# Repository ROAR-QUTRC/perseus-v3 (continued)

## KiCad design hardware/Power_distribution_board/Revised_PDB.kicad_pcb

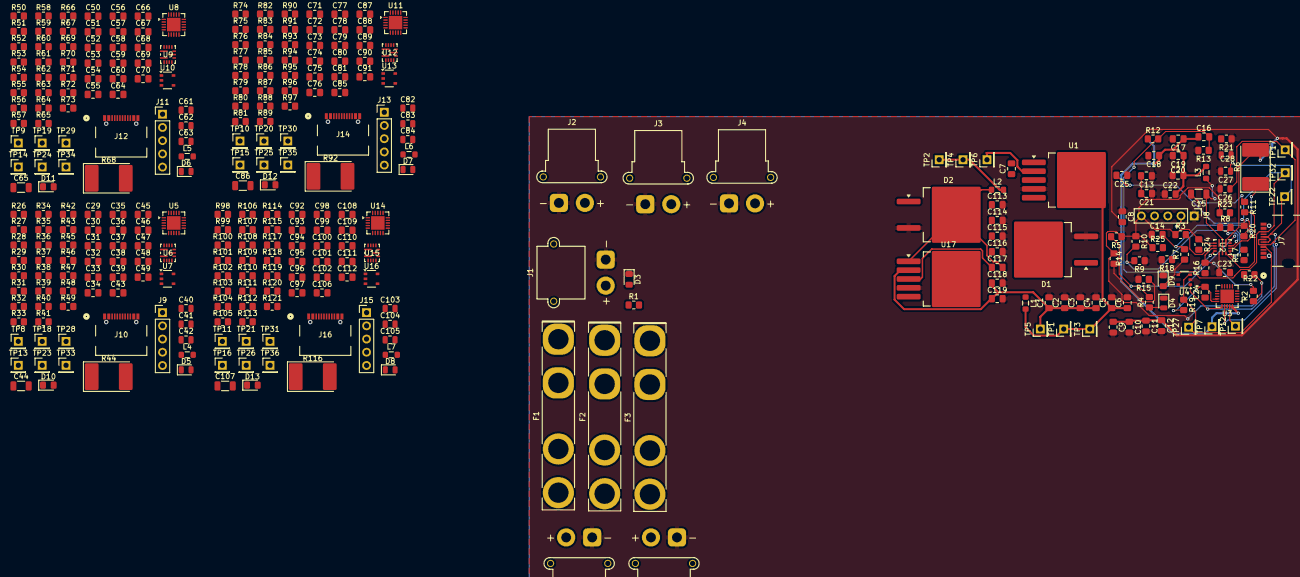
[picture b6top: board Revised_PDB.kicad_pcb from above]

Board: 4 copper layers, 332 parts (0 on the bottom side), 174 nets.

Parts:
C1, C2, C3, C115, C116, C118: 15u; C_0805_2012Metric_Pad1.18x1.45mm_HandSolder
C4, C119: 0.47u; C_0805_2012Metric_Pad1.18x1.45mm_HandSolder
C5, C6, C113, C114: 180u; C_0805_2012Metric_Pad1.18x1.45mm_HandSolder
C7, C117: 0.01u; C_0805_2012Metric_Pad1.18x1.45mm_HandSolder
C8, C31, C52, C73, C94: 100u; C_0805_2012Metric_Pad1.18x1.45mm_HandSolder
C9, C10, C11, C17, C18, C19, C32, C33, C35, C46, C47, C48, C53, C54, C56, C67, C68, C69, C74, C75, C77, C88, C89, C90, C95, C96, C98, C109, C110, C111: 10u; C_0805_2012Metric_Pad1.18x1.45mm_HandSolder
C12, C39, C60, C81, C102: 100n; C_0805_2012Metric_Pad1.18x1.45mm_HandSolder
C13, C21, C22, C29, C30, C38, C50, C51, C59, C71, C72, C80, C92, C93, C101: 2.2u; C_0805_2012Metric_Pad1.18x1.45mm_HandSolder
C14, C45, C66, C87, C108: 1nF; C_0805_2012Metric_Pad1.18x1.45mm_HandSolder
C15, C44, C65, C86, C107: 1u; C_1206_3216Metric
C16, C43, C64, C85, C106: 22pF; C_0805_2012Metric_Pad1.18x1.45mm_HandSolder
C20, C49, C70, C91, C112: 47u; C_0805_2012Metric_Pad1.18x1.45mm_HandSolder
C23, C34, C55, C76, C97: 470n; C_0805_2012Metric_Pad1.18x1.45mm_HandSolder
C24, C25, C36, C37, C57, C58, C78, C79, C99, C100: 390p; C_0805_2012Metric_Pad1.18x1.45mm_HandSolder
C26, C27, C40, C41, C61, C62, C82, C83, C103, C104: 1n; C_0805_2012Metric
C28, C42, C63, C84, C105: 10n; C_0805_2012Metric
D1, D2: 6TQ035S; TO-263-2
D3, D9, D10, D11, D12, D13: LED; LED_0805_2012Metric_Pad1.15x1.40mm_HandSolder
D4, D5, D6, D7, D8: LED; LED_0805_2012Metric
F1, F2: 5A; Fuseholder_Keystone_3555-2
F3: 20A; Fuseholder_Keystone_3555-2
J1: xt30_PWR_IN; AMASS_XT30PW-M_1x02_P2.50mm_Horizontal
J2, J3, J4, J5, J6: XT30_VOUT1; AMASS_XT30PW-F_1x02_P2.50mm_Horizontal
J7, J10, J12, J14, J16: USB_C_Receptacle_USB2.0_16P; USB4105_GCT
J8, J9, J11, J13, J15: Conn_01x05; PinHeader_1x05_P2.54mm_Vertical
L1, L2: L; L_0805_2012Metric_Pad1.05x1.20mm_HandSolder
L3, L4, L5, L6, L7: 4.7u; L_0805_2012Metric_Pad1.05x1.20mm_HandSolder
R1, R18, R30, R54, R78, R102: R; R_0805_2012Metric_Pad1.20x1.40mm_HandSolder
R2, R3, R31, R36, R55, R60, R79, R84, R103, R108: 10k; R_0805_2012Metric_Pad1.20x1.40mm_HandSolder
R4, R5, R39, R40, R63, R64, R87, R88, R111, R112: 2.2k; R_0805_2012Metric_Pad1.20x1.40mm_HandSolder
R6, R44, R68, R92, R116: 300k; D_3220_8050Metric_Pad2.65x5.15mm_HandSolder
R7, R47, R71, R95, R119: 6.8k; R_0805_2012Metric_Pad1.20x1.40mm_HandSolder
R8, R43, R67, R91, R115: 51k; R_0805_2012Metric_Pad1.20x1.40mm_HandSolder
R9, R11, R16, R17, R28, R29, R42, R49, R52, R53, R66, R73, R76, R77, R90, R97, R100, R101, R114, R121: 0; R_0805_2012Metric_Pad1.20x1.40mm_HandSolder
R10, R14, R15, R22, R23, R24, R25, R26, R27, R32, R33, R34, R35, R48, R50, R51, R56, R57, R58, R59, R72, R74, R75, R80, R81, R82, R83, R96, R98, R99, R104, R105, R106, R107, R120: DNF; R_0805_2012Metric_Pad1.20x1.40mm_HandSolder
R12, R45, R69, R93, R117: 100k; R_0805_2012Metric_Pad1.20x1.40mm_HandSolder
R13, R46, R70, R94, R118: 11k; R_0805_2012Metric_Pad1.20x1.40mm_HandSolder
R19, R20, R37, R38, R61, R62, R85, R86, R109, R110: 2.2; R_0805_2012Metric_Pad1.20x1.40mm_HandSolder
R21, R41, R65, R89, R113: 1M; R_0805_2012Metric_Pad1.20x1.40mm_HandSolder
TP1, TP2: Feeback; PinHeader_1x01_P2.54mm_Vertical
TP3, TP4: VOUT; PinHeader_1x01_P2.54mm_Vertical
TP5, TP6: VIN; PinHeader_1x01_P2.54mm_Vertical
TP7, TP8, TP9, TP10, TP11: VBUS; PinHeader_1x01_P2.54mm_Vertical
TP12, TP13, TP14, TP15, TP16: VDRV; PinHeader_1x01_P2.54mm_Vertical
TP17, TP18, TP19, TP20, TP21: DM; PinHeader_1x01_P2.54mm_Vertical
TP22, TP23, TP24, TP25, TP26: DP; PinHeader_1x01_P2.54mm_Vertical
TP27, TP28, TP29, TP30, TP31: CC1; PinHeader_1x01_P2.54mm_Vertical
TP32, TP33, TP34, TP35, TP36: CC2; PinHeader_1x01_P2.54mm_Vertical
U1, U17: LM2678SX-12_NOPB; TO-263-5_TabPin6
U2, U6, U9, U12, U15: MP2491CGQB-Z; QFN-13_2p5MMx3MM_MNP
U3, U5, U8, U11, U14: MP5031GRE-00A3-P; QFN-20-1EP_4x4mm_P0.5mm_EP2.6x2.6mm
U4, U7, U10, U13, U16: TPD4E1U06DBVR; TSOP-5_1.65x3.05mm_P0.95mm

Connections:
+5V: C13.2, C21.2, C29.2, C38.2, C50.2, C59.2, C71.2, C80.2, C92.2, C101.2, J8.5, J9.5, J11.5, J13.5, J15.5, R2.1, R3.1, R5.1, R10.1, R14.1, R22.1, R23.1, R24.1, R25.1, R26.1, R31.1, R32.1, R33.1, R34.1, R35.1, R36.1, R40.1, R48.1, R50.1, R55.1, R56.1, R57.1, R58.1, R59.1, R60.1, R64.1, R72.1, R74.1, R79.1, R80.1, R81.1, R82.1, R83.1, R84.1, R88.1, R96.1, R98.1, R103.1, R104.1, R105.1, R106.1, R107.1, R108.1, R112.1, R120.1, U2.3 (VCC), U3.7 (VCC), U5.7 (VCC), U6.3 (VCC), U8.7 (VCC), U9.3 (VCC), U11.7 (VCC), U12.3 (VCC), U14.7 (VCC), U15.3 (VCC)
/12 Volt Reg1/VOUT: C113.1, C114.1, F2.1, L2.2, TP2.1 (1_1), TP4.1 (1_1), U17.6 (FB)
/12 Volt Reg/VIN: C1.1, C2.1, C3.1, C4.1, C115.1, C116.1, C118.1, C119.1, F3.2, J2.2, J3.2, J4.2, R1.2, TP5.1 (1_1), TP6.1 (1_1), U1.2 (INPUT), U17.2 (INPUT)
/12 Volt Reg/VOUT: C5.1, C6.1, F1.1, L1.2, TP1.1 (1_1), TP3.1 (1_1), U1.6 (FB)
/USB_pd1/GPIO2: R32.2, U5.11 (GPIO2)
/USB_pd1/GPIO3: R33.2, U5.9 (GPIO3)
/USB_pd1/GPIO4: R34.2, U5.10 (GPIO4)
/USB_pd1/GPIO5: R35.2, U5.4 (GPIO5)
/USB_pd1/PG: R39.2, R40.2, U6.13 (PG)
/USB_pd1/SCL: J9.2, U5.2 (SCL)
/USB_pd1/SDA: J9.3, U5.1 (SDA)
/USB_pd1/VIN: C31.2, C32.1, C33.1, C35.1, C39.1, R44.2, U6.1 (IN)
/USB_pd1/VSEL1: R29.2, R36.2, U6.4 (VSEL1)
/USB_pd1/VSEL2: R28.2, R31.2, U6.5 (VSEL2)
/USB_pd2/GPIO2: R56.2, U8.11 (GPIO2)
/USB_pd2/GPIO3: R57.2, U8.9 (GPIO3)
/USB_pd2/GPIO4: R58.2, U8.10 (GPIO4)
/USB_pd2/GPIO5: R59.2, U8.4 (GPIO5)
/USB_pd2/PG: R63.2, R64.2, U9.13 (PG)
/USB_pd2/SCL: J11.2, U8.2 (SCL)
/USB_pd2/SDA: J11.3, U8.1 (SDA)
/USB_pd2/VIN: C52.2, C53.1, C54.1, C56.1, C60.1, R68.2, U9.1 (IN)
/USB_pd2/VSEL1: R53.2, R60.2, U9.4 (VSEL1)
/USB_pd2/VSEL2: R52.2, R55.2, U9.5 (VSEL2)
/USB_pd3/GPIO2: R80.2, U11.11 (GPIO2)
/USB_pd3/GPIO3: R81.2, U11.9 (GPIO3)
/USB_pd3/GPIO4: R82.2, U11.10 (GPIO4)
/USB_pd3/GPIO5: R83.2, U11.4 (GPIO5)
/USB_pd3/PG: R87.2, R88.2, U12.13 (PG)
/USB_pd3/SCL: J13.2, U11.2 (SCL)
/USB_pd3/SDA: J13.3, U11.1 (SDA)
/USB_pd3/VIN: C73.2, C74.1, C75.1, C77.1, C81.1, R92.2, U12.1 (IN)
/USB_pd3/VSEL1: R77.2, R84.2, U12.4 (VSEL1)
/USB_pd3/VSEL2: R76.2, R79.2, U12.5 (VSEL2)
/USB_pd4/GPIO2: R104.2, U14.11 (GPIO2)
/USB_pd4/GPIO3: R105.2, U14.9 (GPIO3)
/USB_pd4/GPIO4: R106.2, U14.10 (GPIO4)
/USB_pd4/GPIO5: R107.2, U14.4 (GPIO5)
/USB_pd4/PG: R111.2, R112.2, U15.13 (PG)
/USB_pd4/SCL: J15.2, U14.2 (SCL)
/USB_pd4/SDA: J15.3, U14.1 (SDA)
/USB_pd4/VIN: C94.2, C95.1, C96.1, C98.1, C102.1, R116.2, U15.1 (IN)
/USB_pd4/VSEL1: R101.2, R108.2, U15.4 (VSEL1)
/USB_pd4/VSEL2: R100.2, R103.2, U15.5 (VSEL2)
/USB_pd/GPIO2: R22.2, U3.11 (GPIO2)
/USB_pd/GPIO3: R23.2, U3.9 (GPIO3)
/USB_pd/GPIO4: R24.2, U3.10 (GPIO4)
/USB_pd/GPIO5: R25.2, U3.4 (GPIO5)
/USB_pd/PG: R4.2, R5.2, U2.13 (PG)
/USB_pd/SCL: J8.2, U3.2 (SCL)
/USB_pd/SDA: J8.3, U3.1 (SDA)
/USB_pd/VIN: C8.2, C9.1, C10.1, C11.1, C12.1, R6.2, U2.1 (IN)
/USB_pd/VSEL1: R3.2, R17.2, U2.4 (VSEL1)
/USB_pd/VSEL2: R2.2, R16.2, U2.5 (VSEL2)
GND: C1.2, C2.2, C3.2, C4.2, C5.2, C6.2, C8.1, C9.2, C10.2, C11.2, C12.2, C13.1, C14.1, C17.2, C18.2, C19.2, C20.2, C21.1, C22.1, C23.1, C24.1, C25.1, C26.2, C27.2, C28.2, C29.1, C30.1, C31.1, C32.2, C33.2, C34.1, C35.2, C36.1, C37.1, C38.1, C39.2, C40.2, C41.2, C42.2, C45.1, C46.2, C47.2, C48.2, C49.2, C50.1, C51.1, C52.1, C53.2, C54.2, C55.1, C56.2, C57.1, C58.1, C59.1, C60.2, C61.2, C62.2, C63.2, C66.1, C67.2, C68.2, C69.2, C70.2, C71.1, C72.1, C73.1, C74.2, C75.2, C76.1, C77.2, C78.1, C79.1, C80.1, C81.2, C82.2, C83.2, C84.2, C87.1, C88.2, C89.2, C90.2, C91.2, C92.1, C93.1, C94.1, C95.2, C96.2, C97.1, C98.2, C99.1, C100.1, C101.1, C102.2, C103.2, C104.2, C105.2, C108.1, C109.2, C110.2, C111.2, C112.2, C113.2, C114.2, C115.2, C116.2, C118.2, C119.2, D1.3 (A), D2.3 (A), D3.1 (K), D4.1 (K), D5.1 (K), D6.1 (K), D7.1 (K), D8.1 (K), D9.1 (K), D10.1 (K), D11.1 (K), D12.1 (K), D13.1 (K), J1.1, J2.1, J3.1, J4.1, J5.1, J6.1, J8.1, J9.1, J11.1, J13.1, J15.1, R8.1, R9.1, R13.2, R15.2, R18.2, R21.1, R27.2, R30.2, R41.1, R43.1, R46.2, R49.1, R51.2, R54.2, R65.1, R67.1, R70.2, R73.1, R75.2, R78.2, R89.1, R91.1, R94.2, R97.1, R99.2, R102.2, R113.1, R115.1, R118.2, R121.1, U1.4 (GND), U2.2 (PGND), U2.7 (AGND), U4.2, U6.2 (PGND), U6.7 (AGND), U7.2, U9.2 (PGND), U9.7 (AGND), U10.2, U12.2 (PGND), U12.7 (AGND), U13.2, U15.2 (PGND), U15.7 (AGND), U16.2, U17.4 (GND)
unnamed: C15.2, R11.1
unnamed: C44.2, R42.1
unnamed: C65.2, R66.1
unnamed: C86.2, R90.1
unnamed: C107.2, R114.1
unnamed: C7.2, D1.2 (K), L1.1, U1.1 (SWITCH_OUTPUT)
unnamed: C117.2, D2.2 (K), L2.1, U17.1 (SWITCH_OUTPUT)
unnamed: D3.2 (A), R1.1
unnamed: D4.2 (A), R4.1
unnamed: D5.2 (A), R39.1
unnamed: D6.2 (A), R63.1
unnamed: D7.2 (A), R87.1
unnamed: D8.2 (A), R111.1
unnamed: D9.2 (A), R7.1
unnamed: D10.2 (A), R47.1
unnamed: D11.2 (A), R71.1
unnamed: D12.2 (A), R95.1
unnamed: D13.2 (A), R119.1
unnamed: F3.1, J1.2
unnamed: F1.2, J5.2
unnamed: F2.2, J6.2
unnamed: J7.A5 (CC1), R19.1, TP27.1 (1_1), U4.3
unnamed: J7.B5 (CC2), R20.1, TP32.1 (1_1), U4.4
unnamed: C28.1, R21.2
unnamed: J8.4, R18.1, U3.5 (I2C_MODE)
unnamed: J9.4, R30.1, U5.5 (I2C_MODE)
unnamed: J10.A5 (CC1), R37.1, TP28.1 (1_1), U7.3
unnamed: J10.B5 (CC2), R38.1, TP33.1 (1_1), U7.4
unnamed: C42.1, R41.2
unnamed: J11.4, R54.1, U8.5 (I2C_MODE)
unnamed: J12.A5 (CC1), R61.1, TP29.1 (1_1), U10.3
unnamed: J12.B5 (CC2), R62.1, TP34.1 (1_1), U10.4
unnamed: C63.1, R65.2
unnamed: J13.4, R78.1, U11.5 (I2C_MODE)
unnamed: J14.A5 (CC1), R85.1, TP30.1 (1_1), U13.3
unnamed: J14.B5 (CC2), R86.1, TP35.1 (1_1), U13.4
unnamed: C84.1, R89.2
unnamed: J15.4, R102.1, U14.5 (I2C_MODE)
unnamed: J16.A5 (CC1), R109.1, TP31.1 (1_1), U16.3
unnamed: J16.B5 (CC2), R110.1, TP36.1 (1_1), U16.4
unnamed: C105.1, R113.2
unnamed: C7.1, U1.3 (CB)
unnamed: R11.2, U2.9 (BST)
unnamed: C14.2, R6.1, R7.2, U2.11 (EN)
unnamed: C16.2, R12.2, R13.1, U2.6 (FB)
unnamed: R8.2, U2.12 (ILIM)
unnamed: R9.2, R10.2, U2.10 (MODE)
unnamed: C15.1, L3.1, U2.8 (SW)
unnamed: C24.2, R19.2, U3.15 (CC1)
unnamed: C25.2, R20.2, U3.14 (CC2)
unnamed: C26.1, J7.A7 (D-), J7.B7 (D-), TP17.1 (1_1), U3.17 (DM)
unnamed: C27.1, J7.A6 (D+), J7.B6 (D+), TP22.1 (1_1), U3.16 (DP), U4.1
unnamed: R17.1, U3.3 (GPIO1)
unnamed: R16.1, U3.12 (GPIO6)
unnamed: R14.2, R15.1, U3.13 (NTC)
unnamed: C23.2, U3.6 (VDD)
unnamed: TP12.1 (1_1), U3.19 (VDRV)
unnamed: C36.2, R37.2, U5.15 (CC1)
unnamed: C37.2, R38.2, U5.14 (CC2)
unnamed: C40.1, J10.A7 (D-), J10.B7 (D-), TP18.1 (1_1), U5.17 (DM)
unnamed: C41.1, J10.A6 (D+), J10.B6 (D+), TP23.1 (1_1), U5.16 (DP), U7.1
unnamed: R29.1, U5.3 (GPIO1)
unnamed: R28.1, U5.12 (GPIO6)
unnamed: R26.2, R27.1, U5.13 (NTC)
unnamed: C34.2, U5.6 (VDD)
unnamed: TP13.1 (1_1), U5.19 (VDRV)
unnamed: R42.2, U6.9 (BST)
unnamed: C45.2, R44.1, R47.2, U6.11 (EN)
unnamed: C43.2, R45.2, R46.1, U6.6 (FB)
unnamed: R43.2, U6.12 (ILIM)
unnamed: R48.2, R49.2, U6.10 (MODE)
unnamed: C44.1, L4.1, U6.8 (SW)
unnamed: C57.2, R61.2, U8.15 (CC1)
unnamed: C58.2, R62.2, U8.14 (CC2)
unnamed: C61.1, J12.A7 (D-), J12.B7 (D-), TP19.1 (1_1), U8.17 (DM)
unnamed: C62.1, J12.A6 (D+), J12.B6 (D+), TP24.1 (1_1), U8.16 (DP), U10.1
unnamed: R53.1, U8.3 (GPIO1)
unnamed: R52.1, U8.12 (GPIO6)
unnamed: R50.2, R51.1, U8.13 (NTC)
unnamed: C55.2, U8.6 (VDD)
unnamed: TP14.1 (1_1), U8.19 (VDRV)
unnamed: R66.2, U9.9 (BST)
unnamed: C66.2, R68.1, R71.2, U9.11 (EN)
unnamed: C64.2, R69.2, R70.1, U9.6 (FB)
unnamed: R67.2, U9.12 (ILIM)
unnamed: R72.2, R73.2, U9.10 (MODE)
unnamed: C65.1, L5.1, U9.8 (SW)
unnamed: C78.2, R85.2, U11.15 (CC1)
unnamed: C79.2, R86.2, U11.14 (CC2)
unnamed: C82.1, J14.A7 (D-), J14.B7 (D-), TP20.1 (1_1), U11.17 (DM)
unnamed: C83.1, J14.A6 (D+), J14.B6 (D+), TP25.1 (1_1), U11.16 (DP), U13.1
unnamed: R77.1, U11.3 (GPIO1)
unnamed: R76.1, U11.12 (GPIO6)
unnamed: R74.2, R75.1, U11.13 (NTC)
unnamed: C76.2, U11.6 (VDD)
unnamed: TP15.1 (1_1), U11.19 (VDRV)
unnamed: R90.2, U12.9 (BST)
unnamed: C87.2, R92.1, R95.2, U12.11 (EN)
unnamed: C85.2, R93.2, R94.1, U12.6 (FB)
unnamed: R91.2, U12.12 (ILIM)
unnamed: R96.2, R97.2, U12.10 (MODE)
unnamed: C86.1, L6.1, U12.8 (SW)
unnamed: C99.2, R109.2, U14.15 (CC1)
unnamed: C100.2, R110.2, U14.14 (CC2)
unnamed: C103.1, J16.A7 (D-), J16.B7 (D-), TP21.1 (1_1), U14.17 (DM)
unnamed: C104.1, J16.A6 (D+), J16.B6 (D+), TP26.1 (1_1), U14.16 (DP), U16.1
unnamed: R101.1, U14.3 (GPIO1)
unnamed: R100.1, U14.12 (GPIO6)
unnamed: R98.2, R99.1, U14.13 (NTC)
unnamed: C97.2, U14.6 (VDD)
unnamed: TP16.1 (1_1), U14.19 (VDRV)
unnamed: R114.2, U15.9 (BST)
unnamed: C108.2, R116.1, R119.2, U15.11 (EN)
unnamed: C106.2, R117.2, R118.1, U15.6 (FB)
unnamed: R115.2, U15.12 (ILIM)
unnamed: R120.2, R121.2, U15.10 (MODE)
unnamed: C107.1, L7.1, U15.8 (SW)
unnamed: C117.1, U17.3 (CB)
VBUS: C16.1, C17.1, C18.1, C19.1, C20.1, C22.2, C30.2, C43.1, C46.1, C47.1, C48.1, C49.1, C51.2, C64.1, C67.1, C68.1, C69.1, C70.1, C72.2, C85.1, C88.1, C89.1, C90.1, C91.1, C93.2, C106.1, C109.1, C110.1, C111.1, C112.1, L3.2, L4.2, L5.2, L6.2, L7.2, R12.1, R45.1, R69.1, R93.1, R117.1, TP7.1 (1_1), TP8.1 (1_1), TP9.1 (1_1), TP10.1 (1_1), TP11.1 (1_1), U3.20 (VBUS_P), U5.20 (VBUS_P), U8.20 (VBUS_P), U11.20 (VBUS_P), U14.20 (VBUS_P)

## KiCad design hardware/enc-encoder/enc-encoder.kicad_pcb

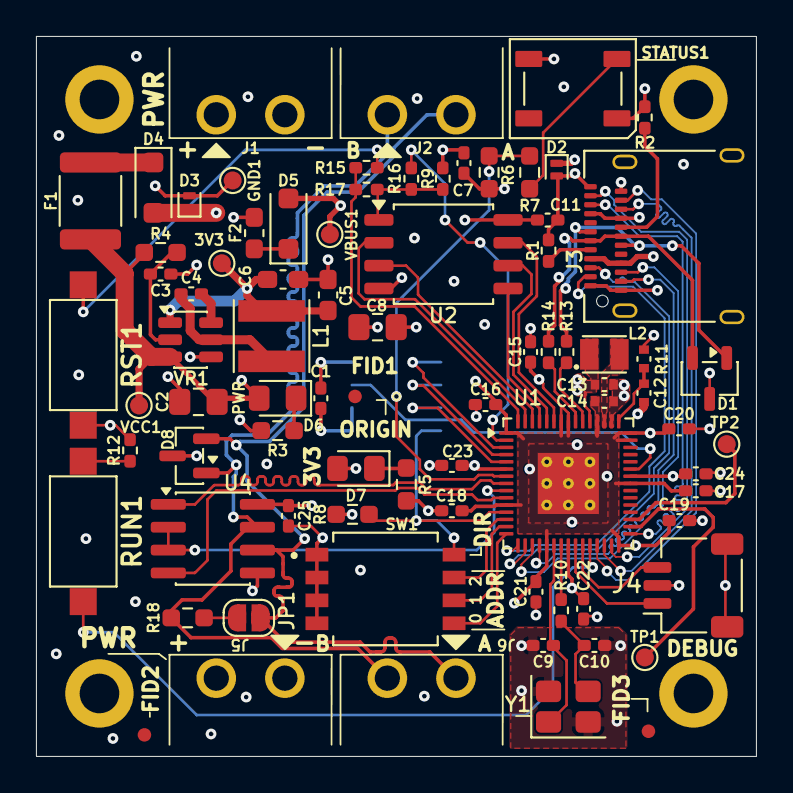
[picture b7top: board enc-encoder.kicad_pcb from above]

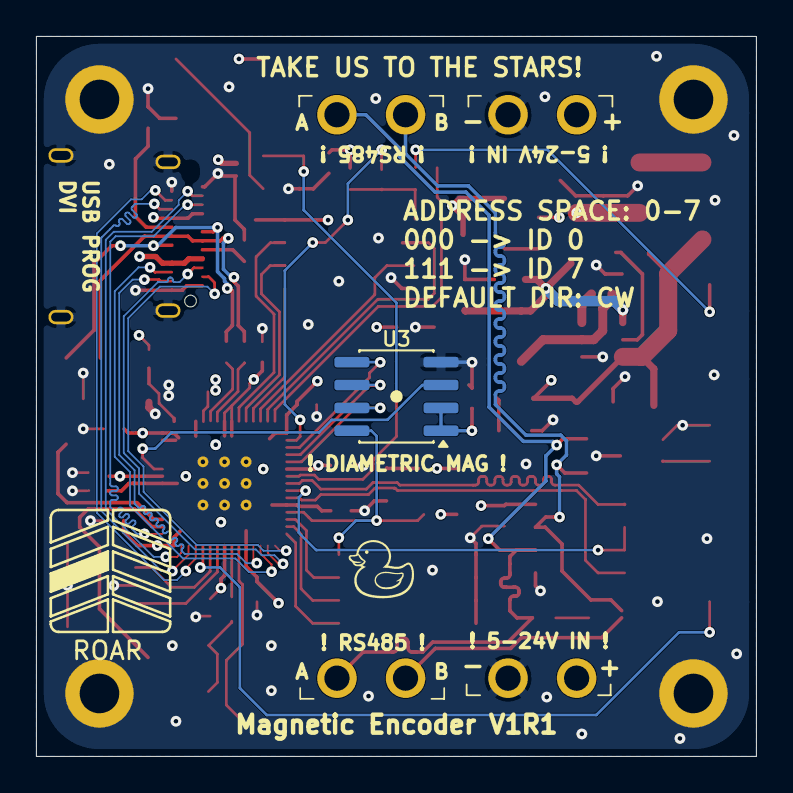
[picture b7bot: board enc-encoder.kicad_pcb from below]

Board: 4 copper layers, 40.0 x 40.0 mm, 86 parts (2 on the bottom side), 63 nets.

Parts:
3V3: Testpoint; TestPoint_Pad_D1.0mm
C1, C3, C4, C7, C11, C15, C16, C17, C18, C19, C20, C21, C23, C24, C25: 100nF; C_0402_1005Metric_Pad0.74x0.62mm_HandSolder
C2, C8: 10uF; C_0805_2012Metric_Pad1.18x1.45mm_HandSolder
C5, C6: 22uF; C_0603_1608Metric_Pad1.08x0.95mm_HandSolder
C9, C10: 15pF; C_0402_1005Metric_Pad0.74x0.62mm_HandSolder
C12, C13, C14: 4.7uF; C_0402_1005Metric_small
C22: 4.7uF; C_0402_1005Metric_Pad0.74x0.62mm_HandSolder
D1: ESDA5V3L; SOT-23-3
D2, D3: PESD1; D_SOD-882
D4, D5: DSS14UTR; D_SOD-123F
D6, D7: GREEN; LED_0805_2012Metric_Pad1.15x1.40mm_HandSolder
D8: SM712_SOT23; SOT-23
F1: 500mA PTC fuse; Fuse_1812_4532Metric
F2: 500mA fast-blow fuse; Fuse_0603_1608Metric_Pad1.05x0.95mm_HandSolder
FID1, FID2, FID3: Fiducial; Fiducial_0.75mm_Mask1.5mm
GND1: Testpoint; TestPoint_Pad_D1.0mm
H1, H2, H3, H4: M2; MountingHole_2.2mm_M2_DIN965_Pad
J1, J2, J5, J6: OQ0232510000G; AnyTek_OQ_3.81mm_90_2P_TriangleKeyLock
J3: USB_C_Receptacle; USB_C_Receptacle_Amphenol_12401610E4-2A
J4: SM03B-SRSS-TB; JST_SH_SM03B-SRSS-TB_1x03-1MP_P1.00mm_Horizontal
JP1: Jumper_2_Small_Open; SolderJumper-2_P1.3mm_Open_RoundedPad1.0x1.5mm
L1: HPC4018NF-4R7M; L_Taiyo-Yuden_MD-4040
L2: 3.3uH; L_Abracon_AOTA-B201610S3R3-101-T
R1, R2: 5.1k; R_0402_1005Metric_Pad0.72x0.64mm_HandSolder
R3, R4, R5, R6, R8: 10k; R_0603_1608Metric_Pad0.98x0.95mm_HandSolder
R7: 470R; R_0603_1608Metric_Pad0.98x0.95mm_HandSolder
R9: 10k; R_0402_1005Metric_Pad0.72x0.64mm_HandSolder
R10, R12, R15: 1k; R_0402_1005Metric_Pad0.72x0.64mm_HandSolder
R11: 33; R_0402_1005Metric_small
R13, R14: 27; R_0402_1005Metric_Pad0.72x0.64mm_HandSolder
R16, R17: 0; R_0402_1005Metric_Pad0.72x0.64mm_HandSolder
R18: 120; R_0603_1608Metric_Pad0.98x0.95mm_HandSolder
RST1: RST; SW_SPST_CK_RS282G05A3
RUN1: RUN; SW_SPST_CK_RS282G05A3
STATUS1: 16347; LED_WS2812B_PLCC4_5.0x5.0mm_P3.2mm
SW1: 219-4LPSTR; SW_218-4LPSTR
TP1, TP2: SPARE_GPIO; TestPoint_Pad_D1.0mm
U1: RP2350A; RP2350A-QFN-60-1EP_7x7mm_P0.4mm_EP3.4x3.4mm
U2: W25Q128JVS; SOIC-8_5.3x5.3mm_P1.27mm
U3: AS5600; SOIC-8_3.9x4.9mm_P1.27mm
U4: SP3485CN; SOIC-8_3.9x4.9mm_P1.27mm
VBUS1: Testpoint; TestPoint_Pad_D1.0mm
VCC1: Testpoint; TestPoint_Pad_D1.0mm
VR1: AP63203WU-7; TSOT-23-6
Y1: ABM8-272-T3; Crystal_SMD_Abracon_ABM8G-4Pin_3.2x2.5mm
ZEH: LOGO

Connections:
+1V1: C13.1, C22.1, C23.1, C24.1, L2.1, U1.6 (DVDD), U1.23 (DVDD), U1.39 (DVDD), U1.50 (VREG_FB)
+3.3V: 3V3.1 (1_1), C1.1, C5.1, C6.1, C7.1, C8.2, C11.1, C14.1, C15.1, C16.1, C17.1, C18.1, C19.1, C20.1, C21.1, C25.1, D7.2 (A), L1.2, R8.2, R9.1, R11.2, STATUS1.1 (VDD), U1.1 (IOVDD), U1.11 (IOVDD), U1.20 (IOVDD), U1.30 (IOVDD), U1.38 (IOVDD), U1.44 (ADC_AVDD), U1.45 (IOVDD), U1.49 (VREG_VIN), U1.53 (USB_OTP_VDD), U1.54 (QSPI_IOVDD), U2.8 (VCC), U3.1 (VDD5V), U3.2 (VDD3V), U4.8 (VCC), VR1.1 (FB)
/HALL_AOUT: U1.40 (GPIO26/ADC0), U3.3 (OUT)
/HALL_DIR: R8.1, SW1.8, U1.12 (GPIO8), U3.8 (DIR)
/HALL_PGO: U1.3 (GPIO1), U3.5 (PGO)
/HALL_SCL: U1.5 (GPIO3), U3.7 (SCL)
/HALL_SDA: U1.4 (GPIO2), U3.6 (SDA)
/ID_ADDR0: SW1.5, U1.15 (GPIO11)
/ID_ADDR1: SW1.6, U1.14 (GPIO10)
/ID_ADDR2: SW1.7, U1.13 (GPIO9)
/RP_HSTX_CK+: J3.B10 (RX1-), U1.18 (GPIO14)
/RP_HSTX_CK-: J3.B11 (RX1+), U1.19 (GPIO15)
/RP_HSTX_D0+: J3.A11 (RX2+), U1.29 (GPIO18)
/RP_HSTX_D0-: J3.A10 (RX2-), U1.31 (GPIO19)
/RP_HSTX_D1+: J3.B2 (TX2+), U1.27 (GPIO16)
/RP_HSTX_D1-: J3.B3 (TX2-), U1.28 (GPIO17)
/RP_HSTX_D2+: J3.A2 (TX1+), U1.16 (GPIO12)
/RP_HSTX_D2-: J3.A3 (TX1-), U1.17 (GPIO13)
/RP_SWCLK: J4.1, U1.24 (SWCLK)
/RP_SWDIO: J4.3, U1.25 (SWDIO)
/RS485_A: D8.2 (A2), J2.2, J6.1, JP1.1 (A), U4.6 (A)
/RS485_B: D8.1 (A1), J2.1, J6.2, R18.2, U4.7 (B)
/RS485_DIR: U1.9 (GPIO6), U4.2 (~RE), U4.3 (DE)
/RS485_RX: U1.8 (GPIO5), U4.1 (RO)
/RS485_TX: U1.10 (GPIO7), U4.4 (DI)
/STATUS_LED: R6.1, R7.1, U1.7 (GPIO4)
/USB_D_N: D1.1 (K1), J3.A7 (D-), J3.B7 (D-), R13.1
/USB_D_P: D1.2 (K2), J3.A6 (D+), J3.B6 (D+), R14.1
/rp2350/FLASH_SS: R9.2, R16.1, R17.1, U2.1 (~CS)
/rp2350/GPIO_0: R16.2, U1.2 (GPIO0)
/rp2350/QSPI_SCLK: U1.56 (QSPI_SCLK), U2.6 (CLK)
/rp2350/QSPI_SD0: U1.57 (QSPI_SD0), U2.5 (DI/IO_{0})
/rp2350/QSPI_SD1: U1.59 (QSPI_SD1), U2.2 (DO/IO_{1})
/rp2350/QSPI_SD2: U1.58 (QSPI_SD2), U2.3 (~WP/IO_{2})
/rp2350/QSPI_SD3: U1.55 (QSPI_SD3), U2.7 (~HOLD/~RESET/IO_{3})
/rp2350/QSPI_SS: R15.1, R17.2, U1.60 (~QSPI_SS)
/rp2350/VREG_LX: L2.2, U1.48 (VREG_LX)
/rp2350/XIN: C9.2, U1.21 (XIN), Y1.1
/rp2350/XOUT: R10.2, U1.22 (XOUT)
/rp2350/~USB_BOOT: R15.2, RST1.2
GND: C1.2, C2.2, C3.2, C5.2, C6.2, C7.2, C8.1, C9.1, C10.1, C11.2, C12.2, C13.2, C14.2, C15.2, C16.2, C17.2, C18.2, C19.2, C20.2, C21.2, C22.2, C23.2, C24.2, C25.2, D1.3 (A), D2.2 (A2), D3.2 (A2), D8.3 (common), GND1.1 (1_1), H1.1 (1_1), H2.1 (1_1), H3.1 (1_1), H4.1 (1_1), J1.2, J3.A1 (GND), J3.A12 (GND), J3.B1 (GND), J3.B12 (GND), J3.SH (SHIELD), J4.2, J4.MP (MountPin), J5.1, R1.2, R2.2, R3.2, R5.2, R6.2, R12.2, RST1.1, STATUS1.3 (VSS), SW1.1, SW1.2, SW1.3, SW1.4, U1.47 (VREG_PGND), U1.61 (GND), U2.4 (GND), U3.4 (GND), U4.5 (GND), VR1.4 (GND), Y1.2 (G), Y1.4 (G)
unnamed: C10.2, R10.1, Y1.3
unnamed: D4.1 (K), F1.2
unnamed: D5.1 (K), F2.1
unnamed: C2.1, D6.2 (A), F1.1, F2.2, R4.1, VCC1.1 (1_1), VR1.3 (IN)
unnamed: D6.1 (K), R3.1
unnamed: D7.1 (K), R5.1
unnamed: J3.A5 (CC1), R1.1
unnamed: J3.B5 (CC2), R2.1
unnamed: JP1.2 (B), R18.1
unnamed: R12.1, RUN1.1
unnamed: R7.2, STATUS1.4 (DIN)
unnamed: TP1.1 (1_1), U1.32 (GPIO20)
unnamed: TP2.1 (1_1), U1.33 (GPIO21)
unnamed: RUN1.2, U1.26 (RUN)
unnamed: R13.2, U1.51 (USB_DM)
unnamed: R14.2, U1.52 (USB_DP)
unnamed: C12.1, R11.1, U1.46 (VREG_AVDD)
unnamed: C4.2, VR1.6 (BST)
unnamed: C3.1, R4.2, VR1.2 (EN)
unnamed: C4.1, L1.1, VR1.5 (SW)
VBUS: D2.1 (A1), D5.2 (A), J3.A4 (VBUS), J3.A9 (VBUS), J3.B4 (VBUS), J3.B9 (VBUS), VBUS1.1 (1_1)
VIN: D3.1 (A1), D4.2 (A), J1.1, J5.2

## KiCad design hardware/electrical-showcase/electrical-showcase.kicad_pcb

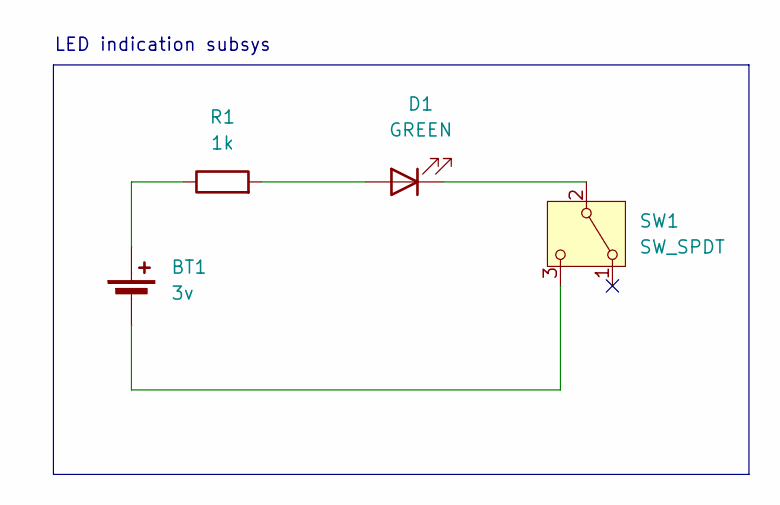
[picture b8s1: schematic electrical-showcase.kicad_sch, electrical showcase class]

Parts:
BT1: 3v; Battery_Panasonic_CR2032-HFN_Horizontal_CircularHoles
D1: GREEN; LED_0603_1608Metric; digikey_part_num 160-LTST-C190GKTCT-ND
R1: 1k; R_0805_2012Metric_Pad1.20x1.40mm_HandSolder
SW1: SW_SPDT; SW_Slide_SPDT_Angled_CK_OS102011MA1Q; digikey_part_num CKN9559-ND

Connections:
unnamed: BT1.1 (+), R1.1
unnamed: BT1.2 (-), SW1.3 (C)
unnamed: D1.2 (A), R1.2
unnamed: D1.1 (K), SW1.2 (B)

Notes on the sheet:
LED indication subsys

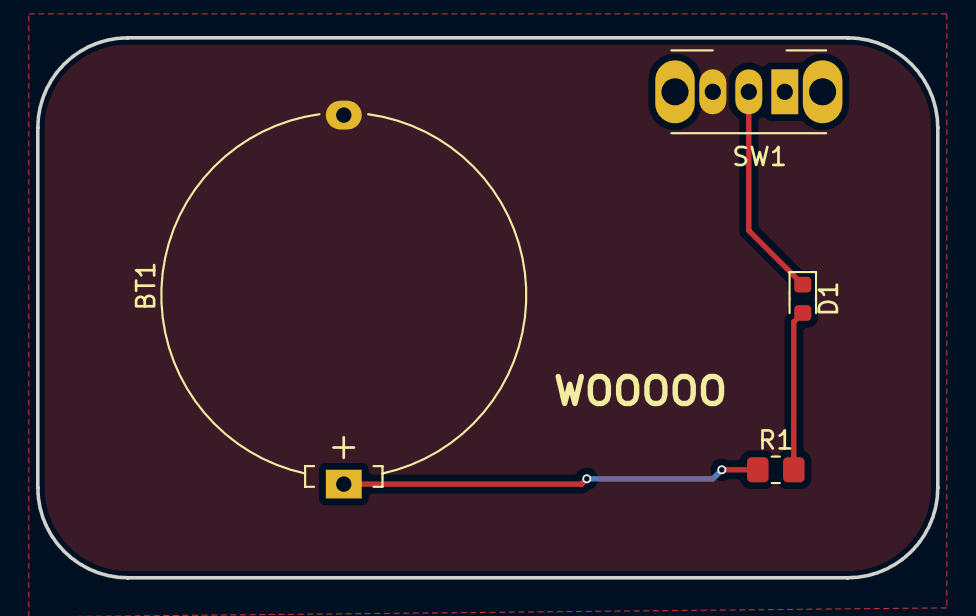
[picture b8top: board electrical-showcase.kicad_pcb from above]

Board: 2 copper layers, 50.0 x 30.0 mm, 4 parts (0 on the bottom side), 4 nets.

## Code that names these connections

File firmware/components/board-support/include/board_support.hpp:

#pragma once

#include <driver/gpio.h>

#include <tuple>

/// @brief Board Support Package - contains board-specific constants and
/// configurations
namespace bsp
{
    /**
     * @brief An ordered pair of GPIO pins.
     *
     * When used for a CAN bus or UART, first pin is for TX, and the second is RX.
     * When used for a motor driver, first pin is for A, and the second is for B.
     */
    typedef std::pair<gpio_num_t, gpio_num_t> pin_pair_t;

    constexpr gpio_num_t CAN_TX_PIN = GPIO_NUM_0;
    constexpr gpio_num_t CAN_RX_PIN = GPIO_NUM_11;

    constexpr gpio_num_t I2C_SDA = GPIO_NUM_35;
    constexpr gpio_num_t I2C_SCL = GPIO_NUM_36;

    constexpr gpio_num_t A1 = GPIO_NUM_1;
    constexpr gpio_num_t A2 = GPIO_NUM_2;
    constexpr gpio_num_t A3 = GPIO_NUM_3;
    constexpr gpio_num_t A4 = GPIO_NUM_4;
    constexpr gpio_num_t A5 = GPIO_NUM_5;
    constexpr gpio_num_t A6 = GPIO_NUM_6;
    constexpr gpio_num_t A7 = GPIO_NUM_7;
    constexpr gpio_num_t A8 = GPIO_NUM_8;
    constexpr gpio_num_t A9 = GPIO_NUM_9;
    constexpr gpio_num_t A10 = GPIO_NUM_10;

    /**
     * @brief One RS485 bus: the UART's TX and RX pins plus the transceiver's
     * direction pin.
     */
    struct rs485_pins_t
    {
        gpio_num_t tx;
        gpio_num_t rx;
        gpio_num_t dir;  // drives the SP3485's DE and ~RE tied together: high = transmit
    };

    // RS485 buses on the dc-motor-driver carrier (hardware/dc-motor-driver,
    // sheets RS485_1 and RS485_2). Named after the schematic nets, whose SBB
    // pins are A7/A8/A9 (bus 1) and A10/IO12/IO39 (bus 2).
    constexpr rs485_pins_t RS485_1 = {A9, A8, A7};                     // MCU1_TX, MCU1_RX, MCU1_DIR
    constexpr rs485_pins_t RS485_2 = {GPIO_NUM_12, A10, GPIO_NUM_39};  // MCU2_TX, MCU2_RX, MCU2_DIR

#if __has_include(<Wire.h>)
    void initI2C();
#endif
}  // namespace bsp

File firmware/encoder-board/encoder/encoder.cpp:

// encoder.cpp
//
// Entry point: one-time board bring-up (DIP-switch ID, AS5600 DIR strap, boot
// banner), then creates the tasks and starts the scheduler.
//   encoder_task (core 1): owns the AS5600
//   comms_task   (core 0): RS485/Modbus RTU slave
//   led_task     (core 0): status LED, must outrank comms_task (see led_task.hpp)

#include <cstdio>

#include "FreeRTOS.h"
#include "comms_task.hpp"
#include "encoder_task.hpp"
#include "hardware/gpio.h"
#include "led_task.hpp"
#include "pico/stdlib.h"
#include "shared_state.hpp"
#include "task.h"

// AS5600 rotation-direction strap: high = CW, low = CCW. Externally pulled up
// (a 4th DIP position can ground it), so read as a plain input.
#ifndef AS5600_DIR_PIN
#define AS5600_DIR_PIN 8
#endif

namespace
{
    // Stack sizes are in words, not bytes.
    constexpr uint32_t kEncoderTaskStackWords = 1024;  // I2C + printf
    constexpr uint32_t kCommsTaskStackWords = 1024;    // RS485/Modbus dispatch + printf
    constexpr uint32_t kLedTaskStackWords = 512;       // just tick() + set_pixel(), no printf

    // led_task must outrank comms_task: see led_task.hpp.
    constexpr UBaseType_t kEncoderTaskPriority = tskIDLE_PRIORITY + 2;
    constexpr UBaseType_t kCommsTaskPriority = tskIDLE_PRIORITY + 1;
    constexpr UBaseType_t kLedTaskPriority = tskIDLE_PRIORITY + 3;

    constexpr UBaseType_t kCore0Affinity = (1u << 0);
    constexpr UBaseType_t kCore1Affinity = (1u << 1);

    // DIP switch (SW1), one bit per pin. A pin is shorted to GND when its
    // switch is on and floats otherwise, so it is read with the internal
    // pull-up: low means the bit is set.
    constexpr uint32_t kBoardIdPin0 = 11;  // ID_ADDR0
    constexpr uint32_t kBoardIdPin1 = 10;  // ID_ADDR1
    constexpr uint32_t kBoardIdPin2 = 9;   // ID_ADDR2

    // Returns the 3-bit device ID (0-7). Call once at boot.
    uint8_t read_board_id()
    {
        gpio_init(kBoardIdPin0);
        gpio_set_dir(kBoardIdPin0, GPIO_IN);
        gpio_pull_up(kBoardIdPin0);

        gpio_init(kBoardIdPin1);
        gpio_set_dir(kBoardIdPin1, GPIO_IN);
        gpio_pull_up(kBoardIdPin1);

        gpio_init(kBoardIdPin2);
        gpio_set_dir(kBoardIdPin2, GPIO_IN);
        gpio_pull_up(kBoardIdPin2);

        sleep_us(10);  // let the pull-ups settle before reading

        uint8_t id = 0;
        if (!gpio_get(kBoardIdPin0))
            id |= (1u << 0);
        if (!gpio_get(kBoardIdPin1))
            id |= (1u << 1);
        if (!gpio_get(kBoardIdPin2))
            id |= (1u << 2);
        return id;
    }
}  // namespace

// Called by the kernel on stack overflow. Halts: memory is already corrupted.
extern "C" void vApplicationStackOverflowHook(TaskHandle_t, char* task_name)
{
    printf("FATAL: stack overflow in task '%s'\n", task_name);
    while (true)
        tight_loop_contents();
}

int main()
{
    stdio_init_all();

    static SharedState shared{};
    shared.device_id = read_board_id();

    gpio_init(AS5600_DIR_PIN);
    gpio_set_dir(AS5600_DIR_PIN, GPIO_IN);
    bool clockwise = gpio_get(AS5600_DIR_PIN);

    // Repeated for a couple of seconds: a monitor opened just after flashing
    // would miss a one-shot print (USB CDC race).
    for (int i = 0; i < 10; ++i)
    {
        printf("device id: %u, direction: %s\n", shared.device_id, clockwise ? "CW" : "CCW");
        sleep_ms(200);
    }

    shared.latest_sample = xQueueCreate(1, sizeof(EncoderSample));
    shared.encoder_commands = xQueueCreate(4, sizeof(EncoderCommand));
    shared.heartbeat_state = xQueueCreate(1, sizeof(HeartbeatState));
    shared.discovery_active = xQueueCreate(1, sizeof(bool));
    configASSERT(shared.latest_sample && shared.encoder_commands && shared.heartbeat_state &&
                 shared.discovery_active);

    // Seed the length-1 queues so the first xQueuePeek() in comms_task/led_task succeeds.
    EncoderSample initial_sample{};
    xQueueOverwrite(shared.latest_sample, &initial_sample);
    HeartbeatState initial_heartbeat{};
    xQueueOverwrite(shared.heartbeat_state, &initial_heartbeat);
    bool initial_discovery = false;
    xQueueOverwrite(shared.discovery_active, &initial_discovery);

    BaseType_t ok = pdPASS;
    ok &= xTaskCreateAffinitySet(encoder_task, "encoder", kEncoderTaskStackWords, &shared,
                                 kEncoderTaskPriority, kCore1Affinity, nullptr);
    ok &= xTaskCreateAffinitySet(comms_task, "comms", kCommsTaskStackWords, &shared,
                                 kCommsTaskPriority, kCore0Affinity, nullptr);
    ok &= xTaskCreateAffinitySet(led_task, "led", kLedTaskStackWords, &shared, kLedTaskPriority,
                                 kCore0Affinity, nullptr);
    configASSERT(ok == pdPASS);

    vTaskStartScheduler();

    // Only reached if the scheduler failed to start (e.g. out of heap).
    printf("FATAL: vTaskStartScheduler() returned\n");
    while (true)
        tight_loop_contents();
}
